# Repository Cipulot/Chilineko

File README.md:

# Chilineko

## Features

- Single piece tray case
- O-ring gasket mount (Friction fit)
- [Unified Daughterboard](https://github.com/ai03-2725/Unified-Daughterboard)
- QMK firmware and VIA
- PCB designed with KiCAD 5.1.10

## Layouts

## Notes

- All files are to be used at your own risk
- As for stabilizers, only PCB snap-ins are supported

Read the files provided in the Resources section for further information.

## Resources

- Introductory document and PCB Order guide [here](https://drive.google.com/drive/folders/1Ks_figqYfMSzfUTn7lY1eMxK4qDpxoYU?usp=sharing)
- Personal KiCad Part Collection with already included components from most used one in keyboard [here](https://github.com/cipulot/cipulot_kicad_parts) (already included as a submodule in this repository)

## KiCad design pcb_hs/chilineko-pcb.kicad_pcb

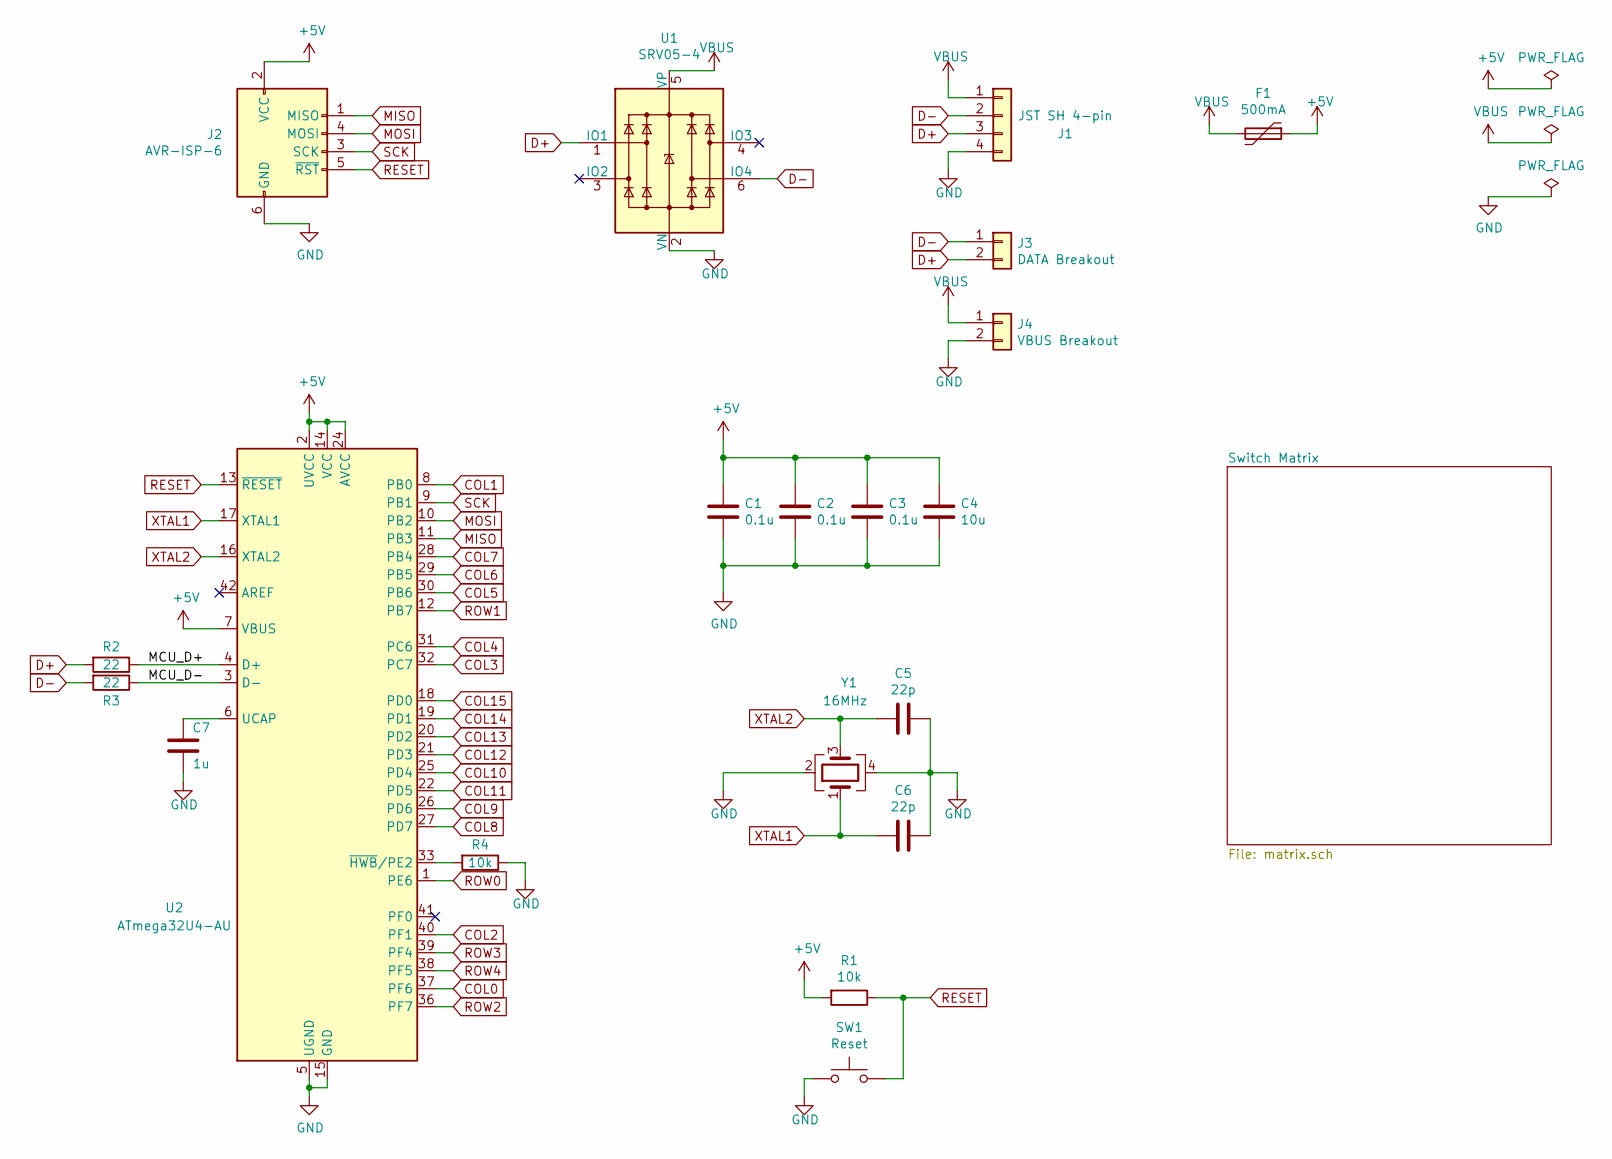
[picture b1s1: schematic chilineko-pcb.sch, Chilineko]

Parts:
C1, C2, C3: 0.1u; C_0805_2012Metric; LCSC Part # C49678
C4: 10u; C_0805_2012Metric; LCSC Part # C15850
C5, C6: 22p; C_0805_2012Metric; LCSC Part # C1804
C7: 1u; C_0805_2012Metric; LCSC Part # C28323
F1: 500mA; Fuse_1206_3216Metric; LCSC Part # C70076
J1: JST SH 4-pin; JST_SH_SM04B-SRSS-TB_1x04-1MP_P1.00mm_Horizontal; LCSC Part # C160404
J2: AVR-ISP-6; Reset_Pretty
J3: DATA Breakout; PinHeader_1x02_P2.54mm_Vertical
J4: VBUS Breakout; PinHeader_1x02_P2.54mm_Vertical
R1, R4: 10k; R_0805_2012Metric; LCSC Part # C17414
R2, R3: 22; R_0805_2012Metric; LCSC Part # C17561
SW1: Reset; SW_SPST_TL3342; LCSC Part # C318884
U1: SRV05-4; SOT-23-6; LCSC Part # C85364
U2: ATmega32U4-AU; TQFP-44_10x10mm_P0.8mm; LCSC Part # C44854
Y1: 16MHz; Crystal_SMD_3225-4Pin_3.2x2.5mm; LCSC Part # C13738

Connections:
+5V: C1.1, C2.1, C3.1, C4.1, F1.1, J2.2 (VCC), R1.2, U2.2 (UVCC), U2.7 (VBUS), U2.14 (VCC), U2.24 (AVCC), U2.34 (VCC), U2.44 (AVCC); also elsewhere on the board
/MCU_D+: R2.1, U2.4 (D+); also elsewhere on the board
/MCU_D-: R3.1, U2.3 (D-); also elsewhere on the board
COL0: U2.37 (PF6); also elsewhere on the board
COL1: U2.8 (PB0); also elsewhere on the board
COL2: U2.40 (PF1); also elsewhere on the board
COL3: U2.32 (PC7); also elsewhere on the board
COL4: U2.31 (PC6); also elsewhere on the board
COL5: U2.30 (PB6); also elsewhere on the board
COL6: U2.29 (PB5); also elsewhere on the board
COL7: U2.28 (PB4); also elsewhere on the board
COL8: U2.27 (PD7); also elsewhere on the board
COL9: U2.26 (PD6); also elsewhere on the board
COL10: U2.25 (PD4); also elsewhere on the board
COL11: U2.22 (PD5); also elsewhere on the board
COL12: U2.21 (PD3); also elsewhere on the board
COL13: U2.20 (PD2); also elsewhere on the board
COL14: U2.19 (PD1); also elsewhere on the board
COL15: U2.18 (PD0); also elsewhere on the board
D+: J1.3, J3.2, R2.2, U1.1 (IO1)
D-: J1.2, J3.1, R3.2, U1.6 (IO4)
GND: C1.2, C2.2, C3.2, C4.2, C5.1, C6.1, C7.1, J1.4, J2.6 (GND), J4.2, R4.1, SW1.1, U1.2 (VN), U2.5 (UGND), U2.15 (GND), U2.23 (GND), U2.35 (GND), U2.43 (GND), Y1.2, Y1.4; also elsewhere on the board
MISO: J2.1 (MISO), U2.11 (PB3); also elsewhere on the board
MOSI: J2.4 (MOSI), U2.10 (PB2); also elsewhere on the board
unnamed 24: C7.2, U2.6 (UCAP); also elsewhere on the board
unnamed 95: R4.2, U2.33 (~HWB~/PE2); also elsewhere on the board
unnamed 98: U2.41 (PF0); also elsewhere on the board
unnamed 99: U2.42 (AREF); also elsewhere on the board
RESET: J2.5 (~RST), R1.1, SW1.2, U2.13 (~RESET); also elsewhere on the board
ROW0: U2.1 (PE6); also elsewhere on the board
ROW1: U2.12 (PB7); also elsewhere on the board
ROW2: U2.36 (PF7); also elsewhere on the board
ROW3: U2.39 (PF4); also elsewhere on the board
ROW4: U2.38 (PF5); also elsewhere on the board
SCK: J2.3 (SCK), U2.9 (PB1); also elsewhere on the board
VBUS: F1.2, J1.1, J4.1, U1.5 (VP)
XTAL1: C6.2, U2.17 (XTAL1), Y1.1; also elsewhere on the board
XTAL2: C5.2, U2.16 (XTAL2), Y1.3; also elsewhere on the board

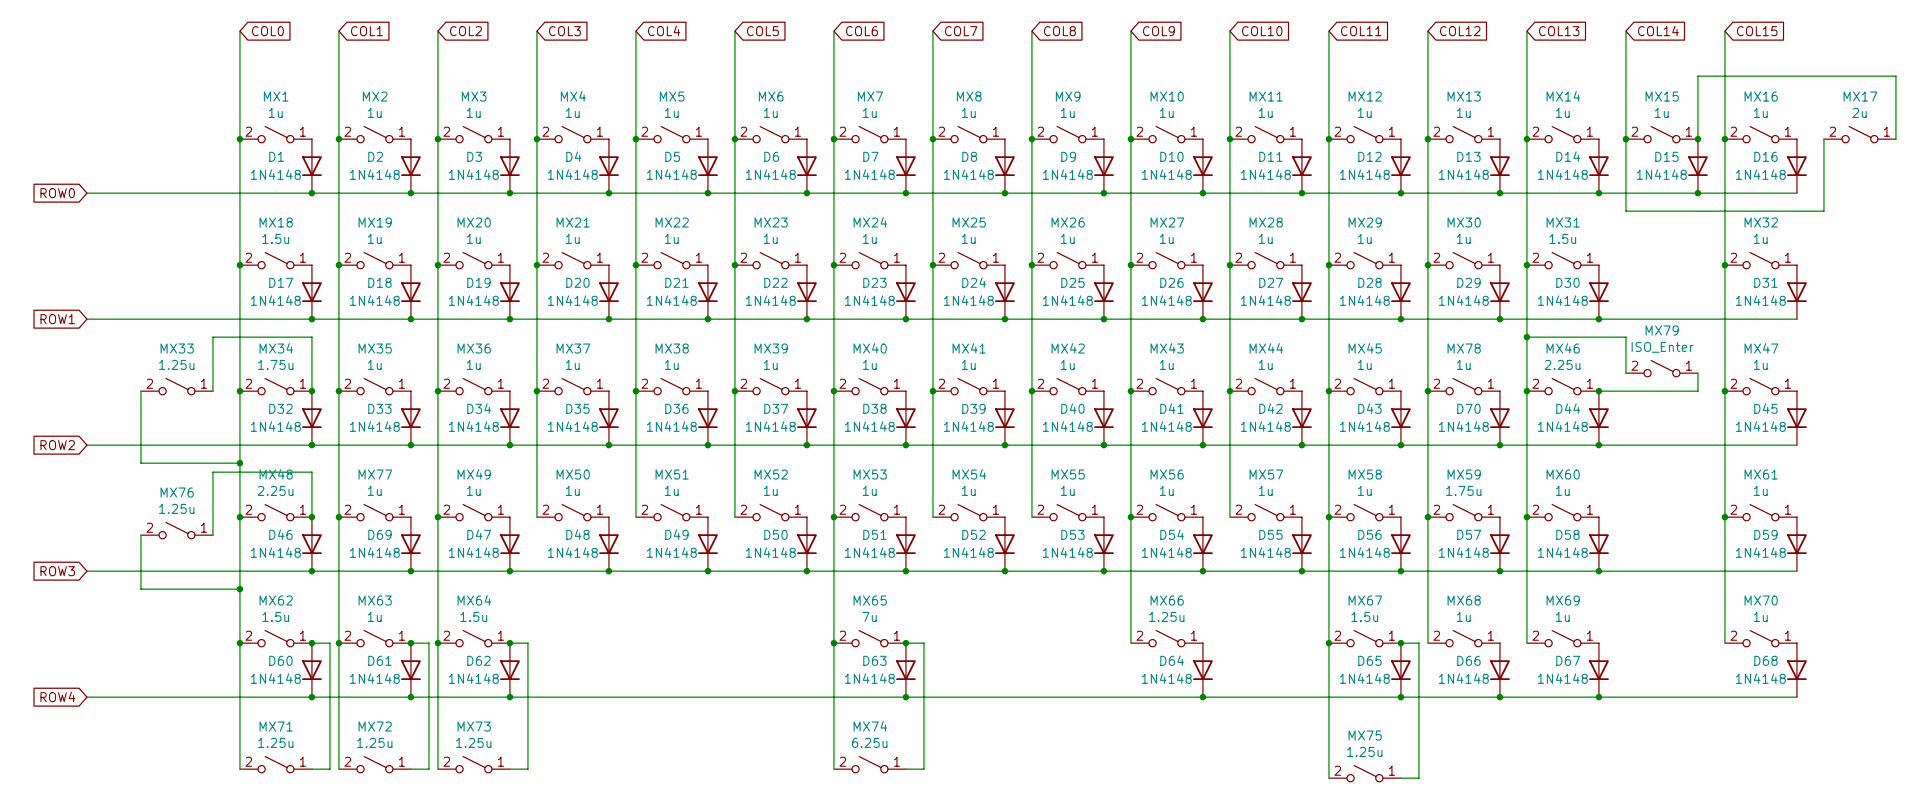
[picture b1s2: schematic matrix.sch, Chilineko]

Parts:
D1, D2, D3, D4, D5, D6, D7, D8, D9, D10, D11, D12, D13, D14, D15, D16, D17, D18, D19, D20, D21, D22, D23, D24, D25, D26, D27, D28, D29, D30, D31, D32, D33, D34, D35, D36, D37, D38, D39, D40, D41, D42, D43, D44, D45, D46, D47, D48, D49, D50, D51, D52, D53, D54, D55, D56, D57, D58, D59, D60, D61, D62, D63, D64, D65, D66, D67, D68, D69, D70: 1N4148; D_SOD-123; LCSC Part # C81598
MX1, MX2, MX3, MX4, MX5, MX6, MX7, MX8, MX9, MX10, MX11, MX12, MX13, MX14, MX15, MX16, MX19, MX20, MX21, MX22, MX23, MX24, MX25, MX26, MX27, MX28, MX29, MX30, MX32, MX35, MX36, MX37, MX38, MX39, MX40, MX41, MX42, MX43, MX44, MX45, MX47, MX49, MX50, MX51, MX52, MX53, MX54, MX55, MX56, MX57, MX58, MX60, MX61, MX63, MX68, MX69, MX70, MX77, MX78: 1u; Kailh_socket_MX_flippin
MX17: 2u; Kailh_socket_MX_flippin
MX18, MX31, MX62, MX64, MX67: 1.5u; Kailh_socket_MX_flippin
MX33, MX66, MX71, MX72, MX73, MX75, MX76: 1.25u; Kailh_socket_MX_flippin
MX34, MX59: 1.75u; Kailh_socket_MX_flippin
MX46, MX48: 2.25u; Kailh_socket_MX_flippin
MX65: 7u; Kailh_socket_MX_flippin
MX74: 6.25u; Kailh_socket_MX_flippin
MX79: ISO_Enter; Kailh_socket_MX_flippin

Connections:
COL0: MX1.2 (B), MX18.2 (B), MX33.2 (B), MX34.2 (B), MX48.2 (B), MX62.2 (B), MX71.2 (B), MX76.2 (B); also elsewhere on the board
COL1: MX2.2 (B), MX19.2 (B), MX35.2 (B), MX63.2 (B), MX72.2 (B), MX77.2 (B); also elsewhere on the board
COL2: MX3.2 (B), MX20.2 (B), MX36.2 (B), MX49.2 (B), MX64.2 (B), MX73.2 (B); also elsewhere on the board
COL3: MX4.2 (B), MX21.2 (B), MX37.2 (B), MX50.2 (B); also elsewhere on the board
COL4: MX5.2 (B), MX22.2 (B), MX38.2 (B), MX51.2 (B); also elsewhere on the board
COL5: MX6.2 (B), MX23.2 (B), MX39.2 (B), MX52.2 (B); also elsewhere on the board
COL6: MX7.2 (B), MX24.2 (B), MX40.2 (B), MX53.2 (B), MX65.2 (B), MX74.2 (B); also elsewhere on the board
COL7: MX8.2 (B), MX25.2 (B), MX41.2 (B), MX54.2 (B); also elsewhere on the board
COL8: MX9.2 (B), MX26.2 (B), MX42.2 (B), MX55.2 (B); also elsewhere on the board
COL9: MX10.2 (B), MX27.2 (B), MX43.2 (B), MX56.2 (B), MX66.2 (B); also elsewhere on the board
COL10: MX11.2 (B), MX28.2 (B), MX44.2 (B), MX57.2 (B); also elsewhere on the board
COL11: MX12.2 (B), MX29.2 (B), MX45.2 (B), MX58.2 (B), MX67.2 (B), MX75.2 (B); also elsewhere on the board
COL12: MX13.2 (B), MX30.2 (B), MX59.2 (B), MX68.2 (B), MX78.2 (B); also elsewhere on the board
COL13: MX14.2 (B), MX31.2 (B), MX46.2 (B), MX60.2 (B), MX69.2 (B), MX79.2 (B); also elsewhere on the board
COL14: MX15.2 (B), MX17.2 (B); also elsewhere on the board
COL15: MX16.2 (B), MX32.2 (B), MX47.2 (B), MX61.2 (B), MX70.2 (B); also elsewhere on the board
unnamed: D1.2 (A), MX1.1 (A)
unnamed: D2.2 (A), MX2.1 (A)
unnamed: D3.2 (A), MX3.1 (A)
unnamed: D4.2 (A), MX4.1 (A)
unnamed: D5.2 (A), MX5.1 (A)
unnamed: D6.2 (A), MX6.1 (A)
unnamed: D7.2 (A), MX7.1 (A)
unnamed: D8.2 (A), MX8.1 (A)
unnamed: D9.2 (A), MX9.1 (A)
unnamed: D10.2 (A), MX10.1 (A)
unnamed: D11.2 (A), MX11.1 (A)
unnamed: D12.2 (A), MX12.1 (A)
unnamed: D13.2 (A), MX13.1 (A)
unnamed: D14.2 (A), MX14.1 (A)
unnamed: D15.2 (A), MX15.1 (A), MX17.1 (A)
unnamed: D16.2 (A), MX16.1 (A)
unnamed: D17.2 (A), MX18.1 (A)
unnamed: D18.2 (A), MX19.1 (A)
unnamed: D19.2 (A), MX20.1 (A)
unnamed: D20.2 (A), MX21.1 (A)
unnamed: D21.2 (A), MX22.1 (A)
unnamed: D22.2 (A), MX23.1 (A)
unnamed: D23.2 (A), MX24.1 (A)
unnamed: D24.2 (A), MX25.1 (A)
unnamed: D25.2 (A), MX26.1 (A)
unnamed: D26.2 (A), MX27.1 (A)
unnamed: D27.2 (A), MX28.1 (A)
unnamed: D28.2 (A), MX29.1 (A)
unnamed: D29.2 (A), MX30.1 (A)
unnamed: D30.2 (A), MX31.1 (A)
unnamed: D31.2 (A), MX32.1 (A)
unnamed: D32.2 (A), MX33.1 (A), MX34.1 (A)
unnamed: D33.2 (A), MX35.1 (A)
unnamed: D34.2 (A), MX36.1 (A)
unnamed: D35.2 (A), MX37.1 (A)
unnamed: D36.2 (A), MX38.1 (A)
unnamed: D37.2 (A), MX39.1 (A)
unnamed: D38.2 (A), MX40.1 (A)
unnamed: D39.2 (A), MX41.1 (A)
unnamed: D40.2 (A), MX42.1 (A)
unnamed: D41.2 (A), MX43.1 (A)
unnamed: D42.2 (A), MX44.1 (A)
unnamed: D43.2 (A), MX45.1 (A)
unnamed: D44.2 (A), MX46.1 (A), MX79.1 (A)
unnamed: D45.2 (A), MX47.1 (A)
unnamed: D46.2 (A), MX48.1 (A), MX76.1 (A)
unnamed: D47.2 (A), MX49.1 (A)
unnamed: D48.2 (A), MX50.1 (A)
unnamed: D49.2 (A), MX51.1 (A)
unnamed: D50.2 (A), MX52.1 (A)
unnamed: D51.2 (A), MX53.1 (A)
unnamed: D52.2 (A), MX54.1 (A)
unnamed: D53.2 (A), MX55.1 (A)
unnamed: D54.2 (A), MX56.1 (A)
unnamed: D55.2 (A), MX57.1 (A)
unnamed: D56.2 (A), MX58.1 (A)
unnamed: D57.2 (A), MX59.1 (A)
unnamed: D58.2 (A), MX60.1 (A)
unnamed: D59.2 (A), MX61.1 (A)
unnamed: D60.2 (A), MX62.1 (A), MX71.1 (A)
unnamed: D61.2 (A), MX63.1 (A), MX72.1 (A)
unnamed: D62.2 (A), MX64.1 (A), MX73.1 (A)
unnamed: D63.2 (A), MX65.1 (A), MX74.1 (A)
unnamed: D64.2 (A), MX66.1 (A)
unnamed: D65.2 (A), MX67.1 (A), MX75.1 (A)
unnamed: D66.2 (A), MX68.1 (A)
unnamed: D67.2 (A), MX69.1 (A)
unnamed: D68.2 (A), MX70.1 (A)
unnamed: D69.2 (A), MX77.1 (A)
unnamed: D70.2 (A), MX78.1 (A)
ROW0: D1.1 (K), D2.1 (K), D3.1 (K), D4.1 (K), D5.1 (K), D6.1 (K), D7.1 (K), D8.1 (K), D9.1 (K), D10.1 (K), D11.1 (K), D12.1 (K), D13.1 (K), D14.1 (K), D15.1 (K), D16.1 (K); also elsewhere on the board
ROW1: D17.1 (K), D18.1 (K), D19.1 (K), D20.1 (K), D21.1 (K), D22.1 (K), D23.1 (K), D24.1 (K), D25.1 (K), D26.1 (K), D27.1 (K), D28.1 (K), D29.1 (K), D30.1 (K), D31.1 (K); also elsewhere on the board
ROW2: D32.1 (K), D33.1 (K), D34.1 (K), D35.1 (K), D36.1 (K), D37.1 (K), D38.1 (K), D39.1 (K), D40.1 (K), D41.1 (K), D42.1 (K), D43.1 (K), D44.1 (K), D45.1 (K), D70.1 (K); also elsewhere on the board
ROW3: D46.1 (K), D47.1 (K), D48.1 (K), D49.1 (K), D50.1 (K), D51.1 (K), D52.1 (K), D53.1 (K), D54.1 (K), D55.1 (K), D56.1 (K), D57.1 (K), D58.1 (K), D59.1 (K), D69.1 (K); also elsewhere on the board
ROW4: D60.1 (K), D61.1 (K), D62.1 (K), D63.1 (K), D64.1 (K), D65.1 (K), D66.1 (K), D67.1 (K), D68.1 (K); also elsewhere on the board

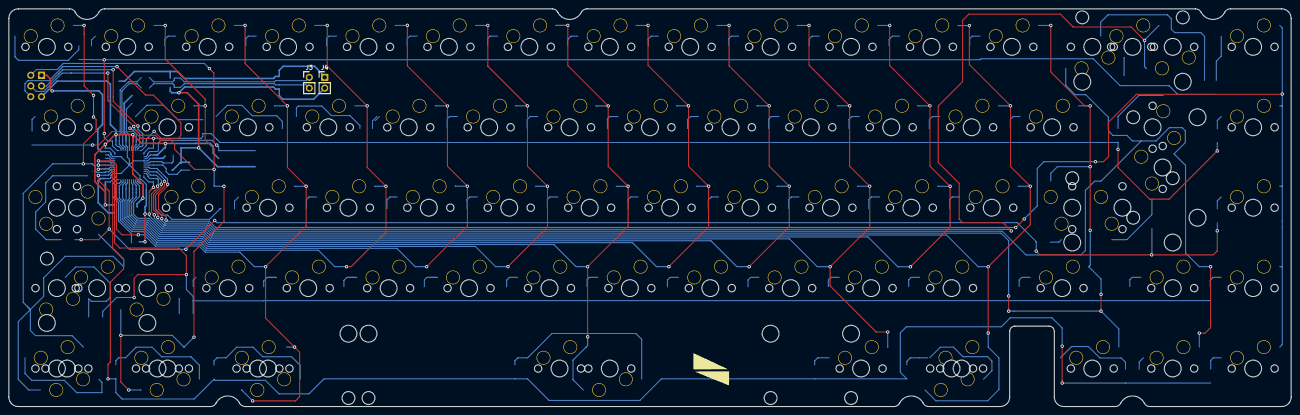
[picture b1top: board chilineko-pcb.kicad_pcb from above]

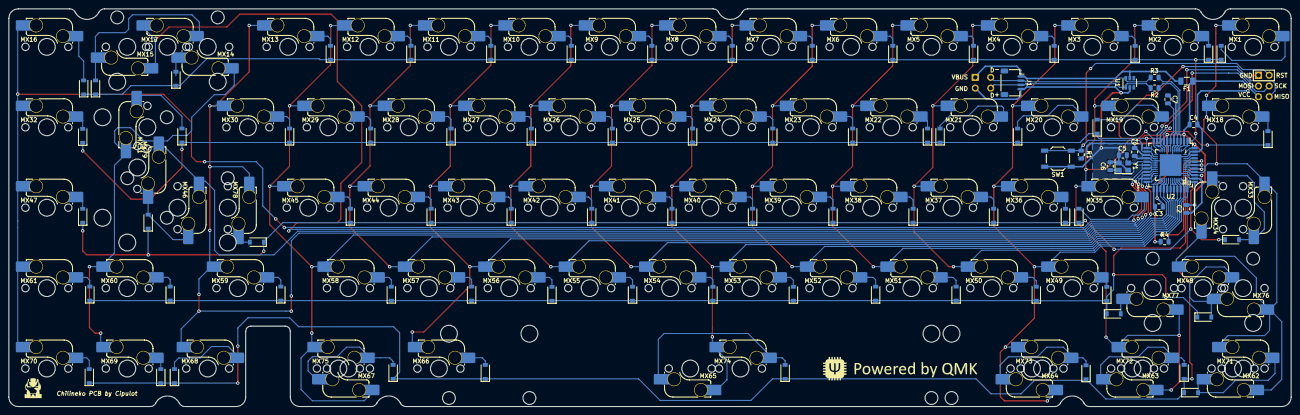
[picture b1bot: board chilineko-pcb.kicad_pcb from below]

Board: 2 copper layers, 303.8 x 94.2 mm, 170 parts (168 on the bottom side), 108 nets.

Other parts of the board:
MU: QFN-44-1EP_7x7mm_P0.5mm_EP5.15x5.15mm

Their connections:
+5V: MU.2, MU.7, MU.14, MU.24, MU.34, MU.44; also elsewhere on the board
/MCU_D+: MU.4; also elsewhere on the board
/MCU_D-: MU.3; also elsewhere on the board
COL0: MU.37; also elsewhere on the board
COL1: MU.8; also elsewhere on the board
COL2: MU.40; also elsewhere on the board
COL3: MU.32; also elsewhere on the board
COL4: MU.31; also elsewhere on the board
COL5: MU.30; also elsewhere on the board
COL6: MU.29; also elsewhere on the board
COL7: MU.28; also elsewhere on the board
COL8: MU.27; also elsewhere on the board
COL9: MU.26; also elsewhere on the board
COL10: MU.25; also elsewhere on the board
COL11: MU.22; also elsewhere on the board
COL12: MU.21; also elsewhere on the board
COL13: MU.20; also elsewhere on the board
COL14: MU.19; also elsewhere on the board
COL15: MU.18; also elsewhere on the board
GND: MU.5, MU.15, MU.23, MU.35, MU.43, MU.45; also elsewhere on the board
MISO: MU.11; also elsewhere on the board
MOSI: MU.10; also elsewhere on the board
unnamed 24: MU.6; also elsewhere on the board
unnamed 95: MU.33; also elsewhere on the board
unnamed 98: MU.41; also elsewhere on the board
unnamed 99: MU.42; also elsewhere on the board
RESET: MU.13; also elsewhere on the board
ROW0: MU.1; also elsewhere on the board
ROW1: MU.12; also elsewhere on the board
ROW2: MU.36; also elsewhere on the board
ROW3: MU.39; also elsewhere on the board
ROW4: MU.38; also elsewhere on the board
SCK: MU.9; also elsewhere on the board
XTAL1: MU.17; also elsewhere on the board
XTAL2: MU.16; also elsewhere on the board

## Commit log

2021-11-19 Upload
2021-11-19 Add submodule
    Submodule containing kicad files and resources
2021-11-19 Gerber .zip folder name change
2021-11-19 Update lib references
2021-11-19 Update of readme and fix in 3d render
2021-11-20 Update of PCB
    Addition of double footprint for MCU. Now the board can be populated with both ATMEGA32U4-AU and ATMEGA32U4-MU.
2021-11-20 Separation of BOM and CPL files
    Separation of files for production based on which MCU package is used.
2021-11-23 Add firmware folder
    The firmware is still in WIP.
    The default ANSI layout is available but the alternative layouts are still in the work.
2021-11-29 Addition of MUR variant production files
2021-12-05 Update firmware for VIA Layouts
2022-08-12 Update to include HS socket in assembly files

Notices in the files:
pcb_hs/chilineko-pcb.sch:
Copyright © 2021 Cipulot
MIT License
